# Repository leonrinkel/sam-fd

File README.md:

# sam-fd

ATSAMC21 based CAN-FD interface

## Initialization

Make sure you have a proper Zephyr development environment according to the official documentation.

```sh
west init -m https://git.leon.fyi/sam-fd-sdk --mr main sam-fd-workspace # or
west init -m https://github.com/leonrinkel/sam-fd-sdk --mr main sam-fd-workspace
cd sam-fd-workspace
west update
```

## Building

```sh
west build --sysbuild -b sam_fd sam-fd-sdk/app
```

## Flashing

### Using a Debugger

```sh
west flash --runner jlink # or
west flash --runner pyocd
```

### Via Serial Recovery

Serial recovery mode can be entered by running a command like the following immediately after resetting.

```sh
mcumgr \
    --conntype serial \
    --connstring dev=/dev/cu.usbserial-110,baud=115200 \
    image upload -e build/app/zephyr/zephyr.signed.bin
```

## License

Please see [hardware/LICENSE](rev1/LICENSE) and [sam-fd-sdk](https://git.leon.fyi/sam-fd-sdk). The software side of this project is based on [Zephyr](https://www.zephyrproject.org) which is mostly licensed under the [Apache-2.0](http://www.apache.org/licenses/LICENSE-2.0) license.

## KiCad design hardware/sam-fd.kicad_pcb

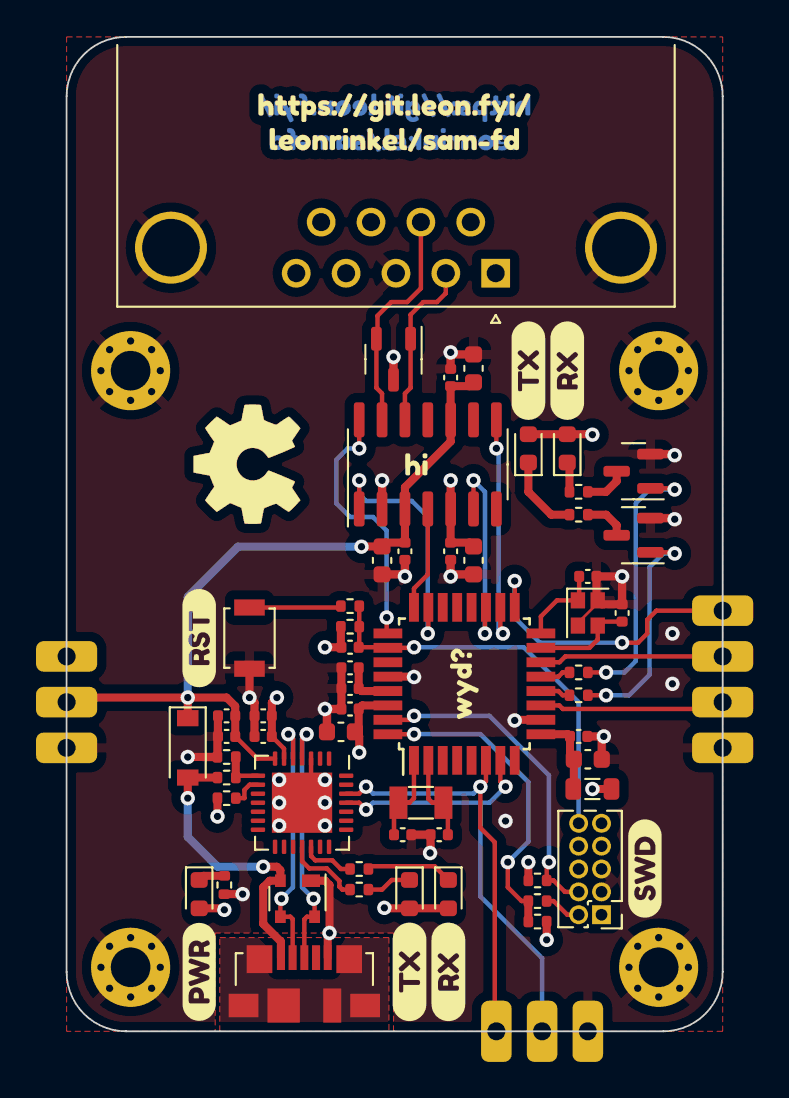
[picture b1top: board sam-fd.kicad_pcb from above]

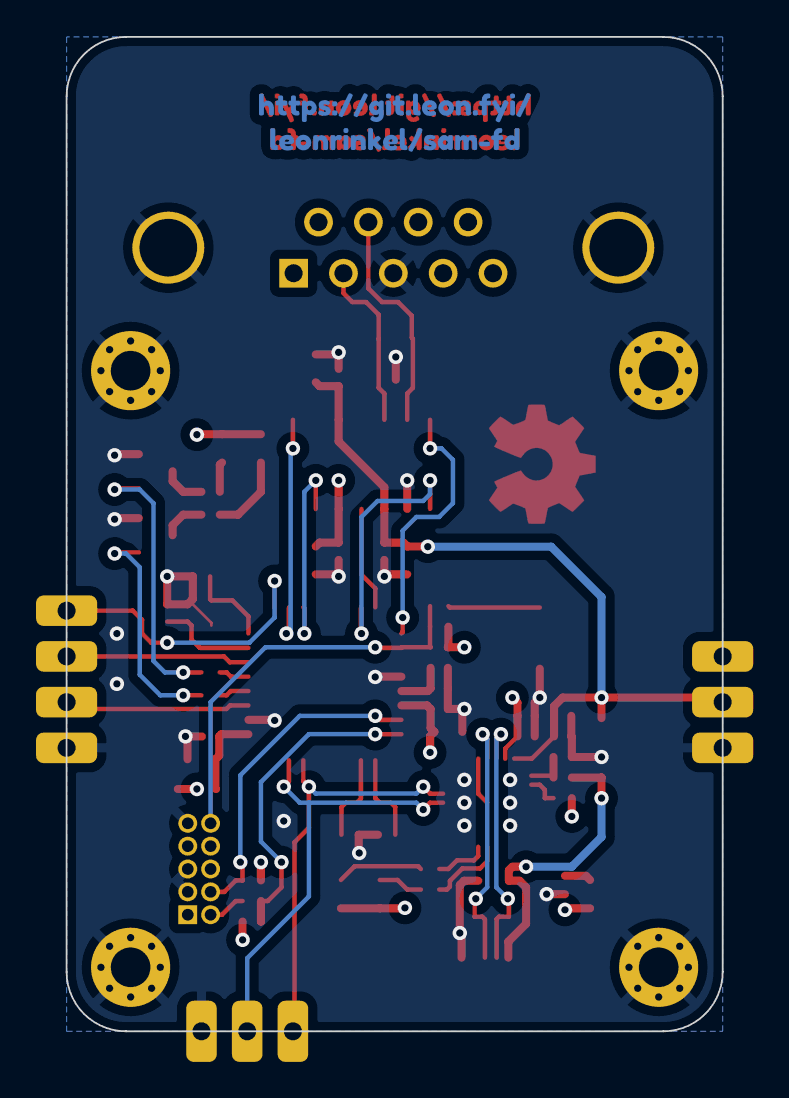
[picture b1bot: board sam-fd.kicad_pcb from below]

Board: 4 copper layers, 36.4 x 55.2 mm, 78 parts (2 on the bottom side), 44 nets.

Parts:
C1: 100pF; C_0402_1005Metric
C2, C3: 4.7pF; C_0402_1005Metric
C4, C7, C16, C18, C19: 10µF; C_0603_1608Metric
C5, C8, C9, C13, C15, C17, C20, C21: 100nF; C_0402_1005Metric
C6: 1µF; C_0402_1005Metric
C10, C11: 5.6pF; C_0402_1005Metric
C12, C14: 4.7µF; C_0402_1005Metric
D1: RED; LED_0603_1608Metric
D2, D3: GREEN; LED_0603_1608Metric
D4: SP0503BAHT; SOT-143
D5: MBR130T1G; D_SOD-123
D6, D7: YELLOW; LED_0603_1608Metric
H1, H2, H3, H4: MountingHole_Pad; MountingHole_2.2mm_M2_Pad_Via
J1: Conn_ARM_JTAG_SWD_10; PinHeader_2x05_P1.27mm_Vertical
J2: USB_B_Micro; USB_Micro-B_Molex_47346-0001
J3: DB9_Male_MountingHoles; DSUB-9_Male_Horizontal_P2.77x2.84mm_EdgePinOffset9.90mm_Hou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
J4: Conn_01x04; CastellatedHoles_1x04_P2.54mm
J5, J6: Conn_01x03; CastellatedHoles_1x03_P2.54mm
L1: 39nH; L_0805_2012Metric
Q1, Q2: Q_NPN_BEC; SOT-23
R1, R2, R3, R12, R13: 68Ω; R_0402_1005Metric
R4: 2.2kΩ; R_0402_1005Metric
R5: 330Ω; R_0402_1005Metric
R6, R7: 10kΩ; R_0402_1005Metric
R8: 22Ω; R_0402_1005Metric
R9: 22.1kΩ; R_0402_1005Metric
R10, R14, R15: 47.5kΩ; R_0402_1005Metric
R11: 1kΩ; R_0402_1005Metric
SW1: SW_Push; SW_SPST_B3U-1000P
U1: ATSAMC21E; TQFP-32_7x7mm_P0.8mm
U2: CP2102N-Axx-xQFN28; QFN-28-1EP_5x5mm_P0.5mm_EP3.35x3.35mm
U3: TJA1443AT; SO-14_3.9x8.65mm_P1.27mm
U4: PESD2CANFD24L; SOT-23-3
Y1: 32.768kHz; Crystal_SMD_3215-2Pin_3.2x1.5mm
Y2: 32MHz; Crystal_SMD_2016-4Pin_2.0x1.6mm
kibuzzard-63D3DC5C, kibuzzard-63D3DC5C#2: G***; kibuzzard-63D3DC5C
kibuzzard-63D3DC15: G***; kibuzzard-63D3DC15
kibuzzard-63D3DC51, kibuzzard-63D3DC51#2: G***; kibuzzard-63D3DC51
kibuzzard-63D40F1D: G***; kibuzzard-63D40F1D
kibuzzard-63D41F74: G***; kibuzzard-63D41F74
kibuzzard-63D420B8: G***; kibuzzard-63D420B8
kibuzzard-63D40257: G***; kibuzzard-63D40257
kibuzzard-63E7A1A7: G***; kibuzzard-63E7A1A7
kibuzzard-63E7A1EC: G***; kibuzzard-63E7A1EC
kibuzzard-63E7A1F6: G***; kibuzzard-63E7A1F6
kibuzzard-63E7A25C: G***; kibuzzard-63E7A25C
kibuzzard-63E7A195: G***; kibuzzard-63E7A195
kibuzzard-63E7A280: G***; kibuzzard-63E7A280

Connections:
+3V3: C1.1, C7.1, C9.1, C14.1, C15.1, C18.1, C20.1, D1.2 (A), D2.2 (A), D3.2 (A), D6.2 (A), D7.2 (A), J1.1 (VTref), J5.1, L1.1, R4.1, R11.1, R14.1, R15.1, U1.30 (VDDIN), U2.6 (VDD), U3.5 (VIO)
+5V: C12.1, C13.1, C16.1, C17.1, C19.1, C21.1, D5.1 (K), J5.2, U2.7 (VREGIN), U3.3 (VCC), U3.10 (VBAT)
/CAN/CAN_HIGH: J3.7, U3.13 (CANH), U4.2
/CAN/CAN_LOW: J3.2, U3.12 (CANL), U4.1
/CAN_EN: U1.19 (PA18), U3.6 (EN)
/CAN_RX: U1.24 (PA25/CAN_RX), U3.4 (RXD)
/CAN_TX: U1.23 (PA24/CAN_TX), U3.1 (TXD)
/CAN_~ERR: U1.18 (PA17), U3.8 (ERR_N)
/CAN_~STB: U1.25 (PA27), U3.14 (STB_N)
/MCU/SWCLK: J1.4 (SWDCLK/TCK), R14.2, U1.31 (PA30/SWCLK)
/MCU/SWDIO: R8.1, R15.2, U1.32 (PA31/SWDIO)
/MCU/VDDANA: C4.1, C5.1, L1.2, U1.9 (VDDANA)
/MCU/VDDCORE: C6.1, C8.1, U1.29 (VDDCORE)
/MCU/XIN: C10.1, U1.15 (PA14/XIN), Y2.3
/MCU/XIN32: C2.2, U1.1 (PA00/XIN32), Y1.2
/MCU/XOUT: C11.1, U1.16 (PA15/XOUT), Y2.1
/MCU/XOUT32: C3.2, U1.2 (PA01/XOUT32), Y1.1
/MCU/~RESET: C1.2, J1.10 (~RESET), R4.2, R5.1, U1.26 (~RESET)
/PA08: J4.2, U1.11 (PA08)
/PA11: J4.3, U1.14 (PA11)
/PA16: J4.4, U1.17 (PA16)
/RX_ACT: R7.1, U1.13 (PA10)
/TX_ACT: R6.1, U1.12 (PA09)
/UART_RX: J6.1, U1.6 (PA05), U2.26 (TXD)
/UART_TX: J6.2, U1.7 (PA06), U2.25 (RXD)
/USB/D+: D4.4 (K), J2.3 (D+), U2.4 (D+)
/USB/D-: D4.3 (K), J2.2 (D-), U2.5 (D-)
/USB/~RXT: R13.1, U2.18 (~RXT/GPIO.1)
/USB/~TXT: R12.1, U2.19 (~TXT/GPIO.0)
GND: C2.1, C3.1, C4.2, C5.2, C6.2, C7.2, C8.2, C9.2, C10.2, C11.2, C12.2, C13.2, C14.2, C15.2, C16.2, C17.2, C18.2, C19.2, C20.2, C21.2, D4.1 (A), H1.1, H2.1, H3.1, H4.1, J1.3 (GND), J1.5 (GND), J1.9 (GNDDetect), J2.5 (GND), J3.0 (PAD), J3.3, J4.1, J5.3, J6.3, Q1.2 (E), Q2.2 (E), R1.2, R10.2, SW1.1, U1.10 (GND), U1.28 (GND), U2.3 (GND), U2.29 (GND), U3.2 (GND), U4.3, Y2.2, Y2.4
unnamed: D1.1 (K), R1.1
unnamed: D2.1 (K), R2.1
unnamed: D3.1 (K), R3.1
unnamed: D6.1 (K), R12.2
unnamed: D7.1 (K), R13.2
unnamed: J1.2 (SWDIO/TMS), R8.2
unnamed: Q1.1 (B), R6.2
unnamed: Q1.3 (C), R2.2
unnamed: Q2.1 (B), R7.2
unnamed: Q2.3 (C), R3.2
unnamed: R5.2, SW1.2
unnamed: R9.2, R10.1, U2.8 (VBUS)
unnamed: R11.2, U2.9 (~RST)
VBUS: D4.2 (K), D5.2 (A), J2.1 (VBUS), R9.1

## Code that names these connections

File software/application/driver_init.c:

/*
 * Code generated from Atmel Start.
 *
 * This file will be overwritten when reconfiguring your Atmel Start project.
 * Please copy examples or other code you want to keep to a separate file
 * to avoid losing it when reconfiguring.
 */

#include "driver_init.h"
#include <peripheral_clk_config.h>
#include <utils.h>
#include <hal_init.h>

struct can_async_descriptor CAN_0;

struct flash_descriptor FLASH_0;

struct usart_sync_descriptor TARGET_IO;

void FLASH_0_CLOCK_init(void)
{

	hri_mclk_set_AHBMASK_NVMCTRL_bit(MCLK);
}

void FLASH_0_init(void)
{
	FLASH_0_CLOCK_init();
	flash_init(&FLASH_0, NVMCTRL);
}

void TARGET_IO_PORT_init(void)
{

	gpio_set_pin_function(PA05, PINMUX_PA05D_SERCOM0_PAD1);

	gpio_set_pin_function(PA06, PINMUX_PA06D_SERCOM0_PAD2);
}

void TARGET_IO_CLOCK_init(void)
{
	hri_gclk_write_PCHCTRL_reg(GCLK, SERCOM0_GCLK_ID_CORE, CONF_GCLK_SERCOM0_CORE_SRC | (1 << GCLK_PCHCTRL_CHEN_Pos));
	hri_gclk_write_PCHCTRL_reg(GCLK, SERCOM0_GCLK_ID_SLOW, CONF_GCLK_SERCOM0_SLOW_SRC | (1 << GCLK_PCHCTRL_CHEN_Pos));
	hri_mclk_set_APBCMASK_SERCOM0_bit(MCLK);
}

void TARGET_IO_init(void)
{
	TARGET_IO_CLOCK_init();
	usart_sync_init(&TARGET_IO, SERCOM0, (void *)NULL);
	TARGET_IO_PORT_init();
}

void delay_driver_init(void)
{
	delay_init(SysTick);
}

void CAN_0_PORT_init(void)
{

	gpio_set_pin_function(PA25, PINMUX_PA25G_CAN0_RX);

	gpio_set_pin_function(PA24, PINMUX_PA24G_CAN0_TX);
}
/**
 * \brief CAN initialization function
 *
 * Enables CAN peripheral, clocks and initializes CAN driver
 */
void CAN_0_init(void)
{
	hri_mclk_set_AHBMASK_CAN0_bit(MCLK);
	hri_gclk_write_PCHCTRL_reg(GCLK, CAN0_GCLK_ID, CONF_GCLK_CAN0_SRC | (1 << GCLK_PCHCTRL_CHEN_Pos));
	can_async_init(&CAN_0, CAN0);
	CAN_0_PORT_init();
}

void system_init(void)
{
	init_mcu();

	// GPIO on PA09

	gpio_set_pin_level(TX_ACT,
	                   // <y> Initial level
	                   // <id> pad_initial_level
	                   // <false"> Low
	                   // <true"> High
	                   true);

	// Set pin direction to output
	gpio_set_pin_direction(TX_ACT, GPIO_DIRECTION_OUT);

	gpio_set_pin_function(TX_ACT, GPIO_PIN_FUNCTION_OFF);

	// GPIO on PA10

	gpio_set_pin_level(RX_ACT,
	                   // <y> Initial level
	                   // <id> pad_initial_level
	                   // <false"> Low
	                   // <true"> High
	                   true);

	// Set pin direction to output
	gpio_set_pin_direction(RX_ACT, GPIO_DIRECTION_OUT);

	gpio_set_pin_function(RX_ACT, GPIO_PIN_FUNCTION_OFF);

	// GPIO on PA17

	// Set pin direction to input
	gpio_set_pin_direction(CAN_ERR, GPIO_DIRECTION_IN);

	gpio_set_pin_pull_mode(CAN_ERR,
	                       // <y> Pull configuration
	                       // <id> pad_pull_config
	                       // <GPIO_PULL_OFF"> Off
	                       // <GPIO_PULL_UP"> Pull-up
	                       // <GPIO_PULL_DOWN"> Pull-down
	                       GPIO_PULL_OFF);

	gpio_set_pin_function(CAN_ERR, GPIO_PIN_FUNCTION_OFF);

	// GPIO on PA18

	gpio_set_pin_level(CAN_EN,
	                   // <y> Initial level
	                   // <id> pad_initial_level
	                   // <false"> Low
	                   // <true"> High
	                   false);

	// Set pin direction to output
	gpio_set_pin_direction(CAN_EN, GPIO_DIRECTION_OUT);

	gpio_set_pin_function(CAN_EN, GPIO_PIN_FUNCTION_OFF);

	// GPIO on PA27

	gpio_set_pin_level(CAN_STB,
	                   // <y> Initial level
	                   // <id> pad_initial_level
	                   // <false"> Low
	                   // <true"> High
	                   false);

	// Set pin direction to output
	gpio_set_pin_direction(CAN_STB, GPIO_DIRECTION_OUT);

	gpio_set_pin_function(CAN_STB, GPIO_PIN_FUNCTION_OFF);

	FLASH_0_init();

	TARGET_IO_init();

	delay_driver_init();
	CAN_0_init();
}

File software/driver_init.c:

/*
 * Code generated from Atmel Start.
 *
 * This file will be overwritten when reconfiguring your Atmel Start project.
 * Please copy examples or other code you want to keep to a separate file
 * to avoid losing it when reconfiguring.
 */

#include "driver_init.h"
#include <peripheral_clk_config.h>
#include <utils.h>
#include <hal_init.h>

struct can_async_descriptor CAN_0;

struct usart_sync_descriptor TARGET_IO;

void TARGET_IO_PORT_init(void)
{

	gpio_set_pin_function(PA14, PINMUX_PA14C_SERCOM2_PAD2);

	gpio_set_pin_function(PA15, PINMUX_PA15C_SERCOM2_PAD3);
}

void TARGET_IO_CLOCK_init(void)
{
	hri_gclk_write_PCHCTRL_reg(GCLK, SERCOM2_GCLK_ID_CORE, CONF_GCLK_SERCOM2_CORE_SRC | (1 << GCLK_PCHCTRL_CHEN_Pos));
	hri_gclk_write_PCHCTRL_reg(GCLK, SERCOM2_GCLK_ID_SLOW, CONF_GCLK_SERCOM2_SLOW_SRC | (1 << GCLK_PCHCTRL_CHEN_Pos));
	hri_mclk_set_APBCMASK_SERCOM2_bit(MCLK);
}

void TARGET_IO_init(void)
{
	TARGET_IO_CLOCK_init();
	usart_sync_init(&TARGET_IO, SERCOM2, (void *)NULL);
	TARGET_IO_PORT_init();
}

void delay_driver_init(void)
{
	delay_init(SysTick);
}

void CAN_0_PORT_init(void)
{

	gpio_set_pin_function(PA25, PINMUX_PA25G_CAN0_RX);

	gpio_set_pin_function(PA24, PINMUX_PA24G_CAN0_TX);
}
/**
 * \brief CAN initialization function
 *
 * Enables CAN peripheral, clocks and initializes CAN driver
 */
void CAN_0_init(void)
{
	hri_mclk_set_AHBMASK_CAN0_bit(MCLK);
	hri_gclk_write_PCHCTRL_reg(GCLK, CAN0_GCLK_ID, CONF_GCLK_CAN0_SRC | (1 << GCLK_PCHCTRL_CHEN_Pos));
	can_async_init(&CAN_0, CAN0);
	CAN_0_PORT_init();
}

void system_init(void)
{
	init_mcu();

	// GPIO on PA05

	// Set pin direction to input
	gpio_set_pin_direction(BTN, GPIO_DIRECTION_IN);

	gpio_set_pin_pull_mode(BTN,
	                       // <y> Pull configuration
	                       // <id> pad_pull_config
	                       // <GPIO_PULL_OFF"> Off
	                       // <GPIO_PULL_UP"> Pull-up
	                       // <GPIO_PULL_DOWN"> Pull-down
	                       GPIO_PULL_OFF);

	gpio_set_pin_function(BTN, GPIO_PIN_FUNCTION_OFF);

	// GPIO on PA09

	gpio_set_pin_level(RX_ACT,
	                   // <y> Initial level
	                   // <id> pad_initial_level
	                   // <false"> Low
	                   // <true"> High
	                   true);

	// Set pin direction to output
	gpio_set_pin_direction(RX_ACT, GPIO_DIRECTION_OUT);

	gpio_set_pin_function(RX_ACT, GPIO_PIN_FUNCTION_OFF);

	// GPIO on PA10

	gpio_set_pin_level(TX_ACT,
	                   // <y> Initial level
	                   // <id> pad_initial_level
	                   // <false"> Low
	                   // <true"> High
	                   true);

	// Set pin direction to output
	gpio_set_pin_direction(TX_ACT, GPIO_DIRECTION_OUT);

	gpio_set_pin_function(TX_ACT, GPIO_PIN_FUNCTION_OFF);

	// GPIO on PA17

	// Set pin direction to input
	gpio_set_pin_direction(CAN_ERR, GPIO_DIRECTION_IN);

	gpio_set_pin_pull_mode(CAN_ERR,
	                       // <y> Pull configuration
	                       // <id> pad_pull_config
	                       // <GPIO_PULL_OFF"> Off
	                       // <GPIO_PULL_UP"> Pull-up
	                       // <GPIO_PULL_DOWN"> Pull-down
	                       GPIO_PULL_OFF);

	gpio_set_pin_function(CAN_ERR, GPIO_PIN_FUNCTION_OFF);

	// GPIO on PA18

	gpio_set_pin_level(CAN_EN,
	                   // <y> Initial level
	                   // <id> pad_initial_level
	                   // <false"> Low
	                   // <true"> High
	                   false);

	// Set pin direction to output
	gpio_set_pin_direction(CAN_EN, GPIO_DIRECTION_OUT);

	gpio_set_pin_function(CAN_EN, GPIO_PIN_FUNCTION_OFF);

	TARGET_IO_init();

	delay_driver_init();
	CAN_0_init();
}

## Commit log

2023-01-15 add mcu & usb schematic
2023-01-19 move inside hardware dir
2023-01-19 add software from atmel start
2023-01-19 add can 500kbits demo code
2023-01-19 add can transceiver
2023-01-21 can works, try fd now
2023-01-23 worked on it
2023-01-24 picked parts
2023-01-26 did a little routing
2023-01-27 ordered, pray this works
2023-02-11 yay this seems to work
2023-02-11 leds through transistor, castellated holes
2023-02-25 leds now active high
2023-04-08 move application to subfolder
2023-04-08 offset application in flash
2023-04-08 add serial bootloader
2023-04-08 add serial flashing tool
2023-04-08 change flashing baud to 115200
2023-04-08 build application with cmake
2023-04-08 build bootloader with cmake
2023-04-08 remove unused baud arg
2023-04-08 build flash tool using cmake
2023-04-08 add windows support for flasher
2023-04-08 update readme with build/flash instructions
2023-04-08 this and that
2023-04-15 add vscode workspace
2023-04-15 add a bare metal blinky app without atmel start
2023-04-15 add doxygen
2023-04-15 configure doxygen
2023-04-15 document some stuff
2023-04-15 use doxygen with cmake
2023-04-16 oooops actually use build_doc option
2023-04-16 add vscode debugging
2023-04-16 add baremetal gclk helper
2023-04-16 read cpuid
2023-04-16 add optimization
2023-04-16 this and that and so on
2023-08-27 Fix for building flasher with Visual Studio MSVC
2023-08-27 Remove leftover Makefile
2023-08-27 Add some more build instructions
2023-08-27 Add render to README
2023-09-18 Refactor flasher serial stuff
2023-09-18 Add boot cmd to start application after flashing
2023-09-18 Add bootloader stop/stop commands
2023-09-18 Check an application header when booting
2023-09-19 Check number of bytes flashed, allow setting a version number
2023-09-20 Add flash driver for application
2023-09-20 Application integrity checking
2023-09-21 Create flasher.yml
    Try out GitHub actions
2023-09-21 Update flasher.yml
    Only trigger flasher build if there are changes in flasher subdir
2023-09-21 Move flasher CRC stuff in its own file
2023-09-21 Didnt like this baremetal approach
2023-09-21 Baremetal blinky and uart
2023-09-22 Use external oscillator
2023-09-22 Try out interrupts
2023-09-23 Clock failure detection is so cool
2023-09-23 Add 1ms SysTick interrupt
2023-09-23 Use SysTick to call cyclic tasks
2023-09-23 Remove arbitrary delay from UART transmission
2023-09-23 Async UART with ring buffer
2023-09-23 Documentation
2023-09-24 Add baremetal CAN driver
2023-09-24 Make baremetal app bootable by setting vector table offset
2023-09-24 Add UART read
2023-09-24 Add initial flash driver
2023-09-24 Rename some stuff
2023-09-25 Yay figured out baremetal flash writes
2023-10-01 Add baremetal hardware accelerated CRC
2023-10-01 Move common stuff to shared folder
2023-10-01 Add flash write row function
2023-10-01 UART read/write functions
2023-10-01 Add port in register
2023-10-02 Move some stuff
2023-10-11 Mention sam-fd-sdk in README
2023-10-11 Cleanup
2023-10-12 Add basic rev2 schematic
2023-10-16 Update software instructions
2023-10-16 Fix README paths
